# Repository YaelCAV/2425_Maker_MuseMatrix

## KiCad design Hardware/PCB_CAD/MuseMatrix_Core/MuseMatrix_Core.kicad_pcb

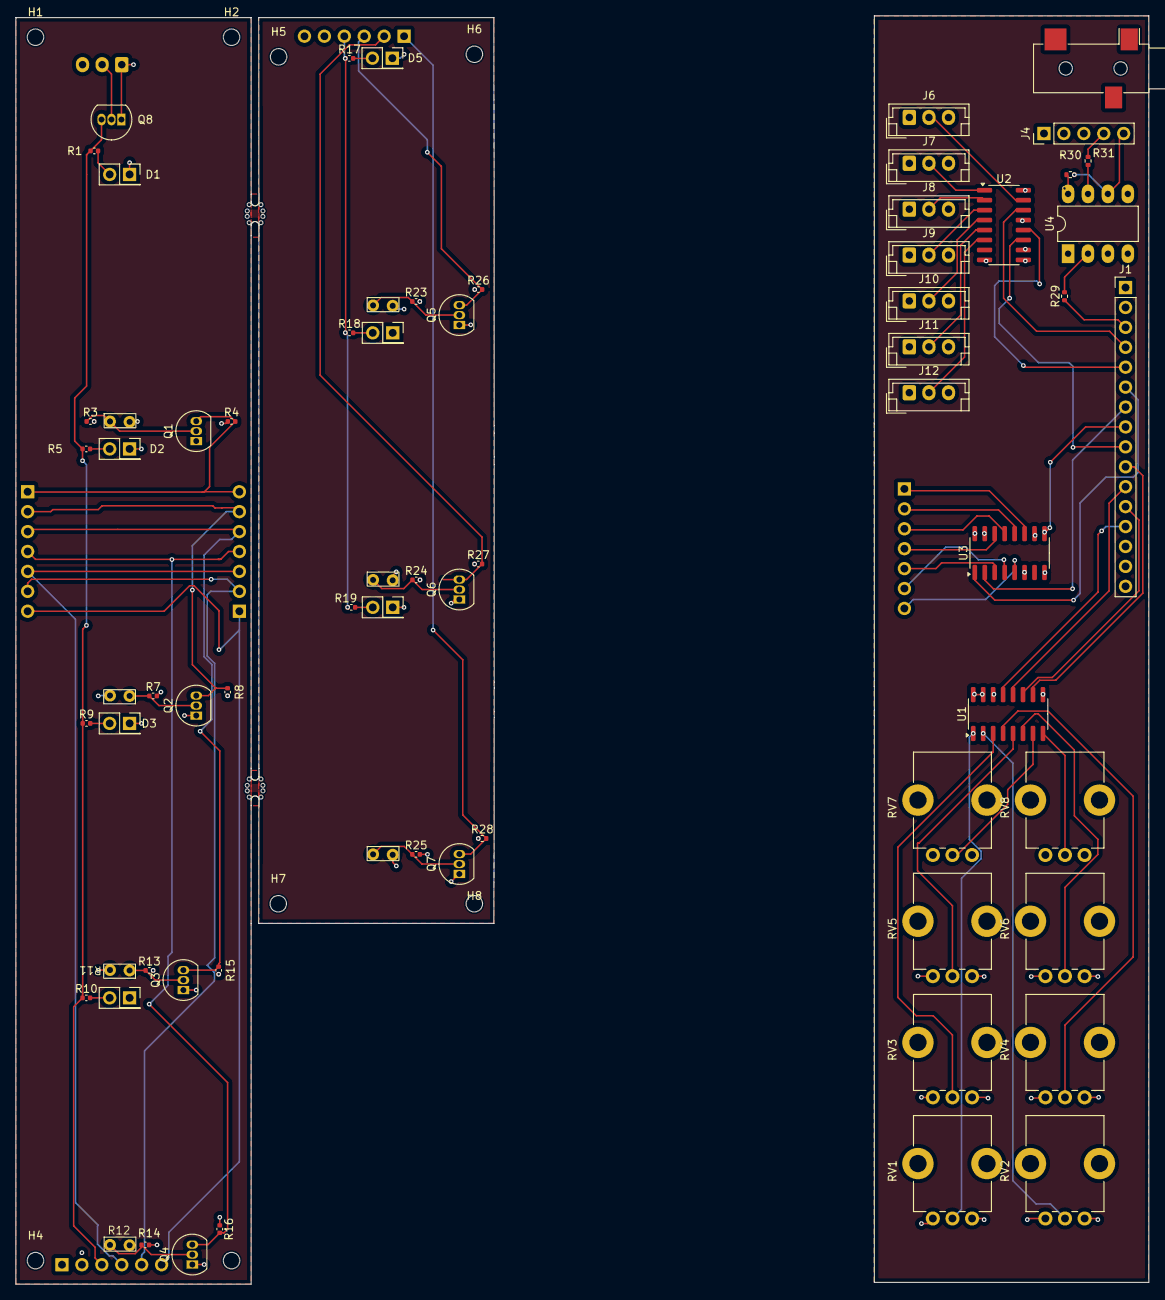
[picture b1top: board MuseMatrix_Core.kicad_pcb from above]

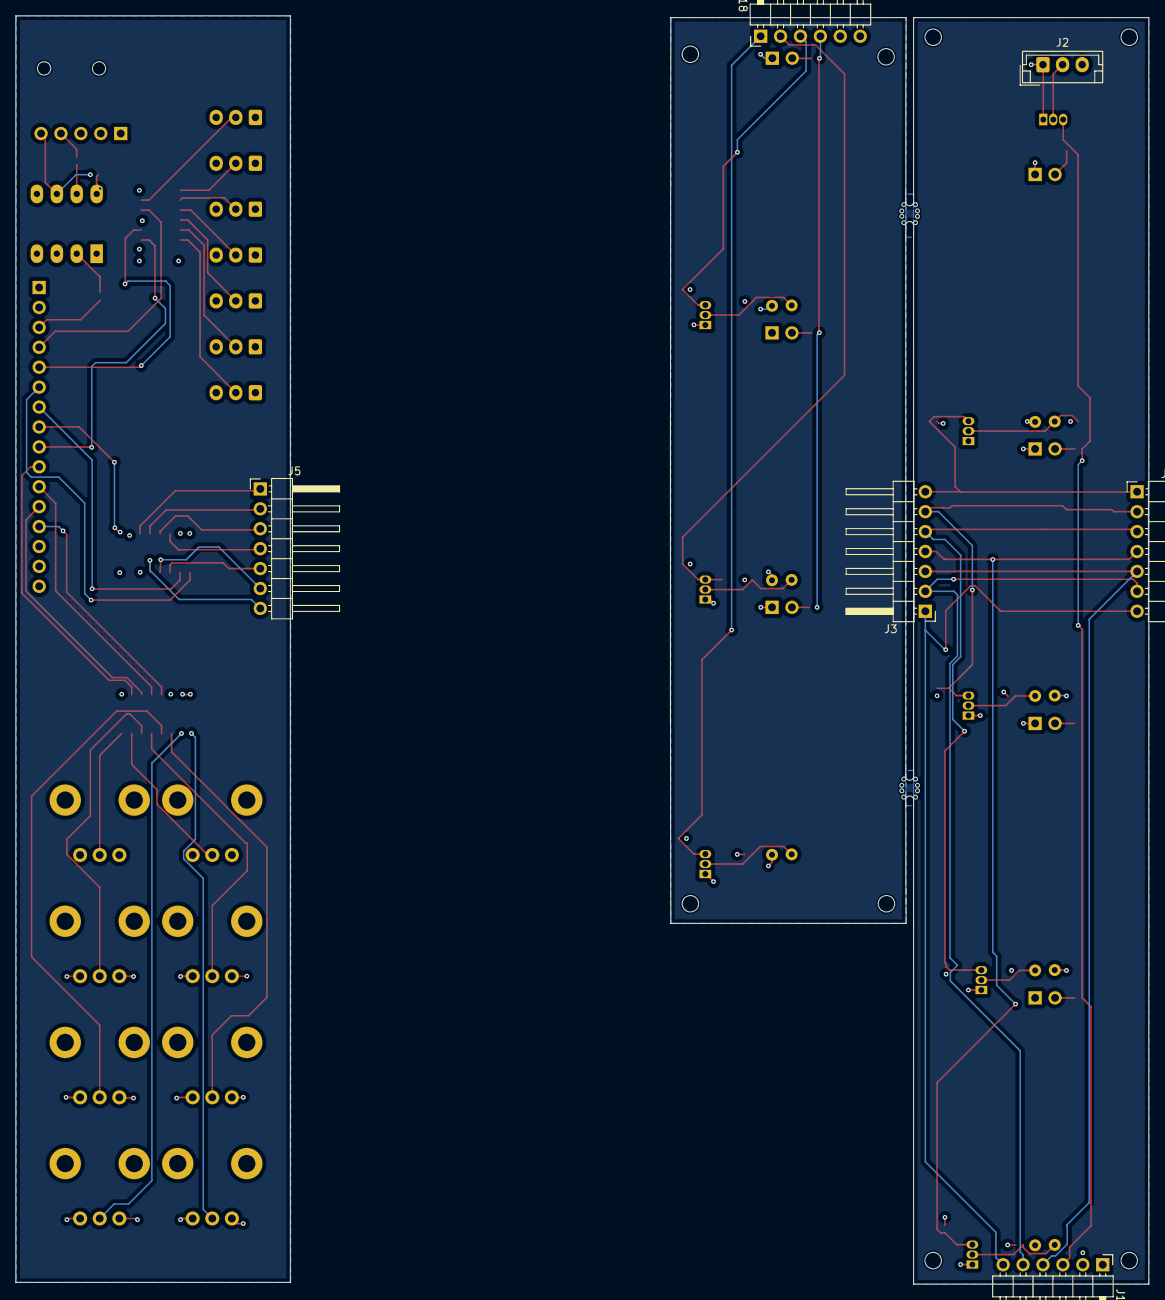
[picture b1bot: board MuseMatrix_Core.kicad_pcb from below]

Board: 4 copper layers, 144.5 x 161.7 mm, 84 parts (6 on the bottom side), 66 nets.

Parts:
D1, D2, D3, D4, D5, D6, D7: LED; PinSocket_2x01_P2.54mm_Vertical
H1, H2, H3, H4, H5, H6, H7, H8: MountingHole; MountingHole_2.1mm
J1: Raspberry_Pi_4; PinHeader_1x16_P2.54mm_Vertical
J2, J6, J7, J8, J9, J10, J11, J12: Conn_01x03_Pin; JST_EH_B3B-EH-A_1x03_P2.50mm_Vertical
J3: Conn_01x10_Socket; PinHeader_1x07_P2.54mm_Horizontal
J4: DIN-5; PinHeader_1x05_P2.54mm_Vertical
J5, J13: Conn_01x07_Socket; PinHeader_1x07_P2.54mm_Horizontal
J14: Jack-DC; Jack_3.5mm_CUI_SJ-3523-SMT_Horizontal
J17, J18: Conn_01x06_Pin; PinHeader_1x06_P2.54mm_Horizontal
Q1, Q2, Q3, Q4, Q5, Q6, Q7, Q8: 2N3904; TO-92_Inline
R1, R5, R9, R10, R17, R18, R19: 330; C_0402_1005Metric
R2, R6, R11, R12, R20, R21, R22: LDR07; LDR 2.5 horizontal
R3, R4, R7, R8, R13, R14, R15, R16, R23, R24, R25, R26, R27: 10k; C_0402_1005Metric
R28: 10k; R_0402_1005Metric
R29, R30, R31: 330; R_0402_1005Metric
RV1, RV2, RV3, RV4, RV5, RV6, RV7, RV8: R_Potentiometer; Potentiometer_Bourns_PTV09A-1_Single_Vertical
U1: MCP3008; SOIC-16_3.9x9.9mm_P1.27mm
U2: 74HC595; SOIC-16_3.9x9.9mm_P1.27mm
U3: 74HC165; SOIC-16_3.9x9.9mm_P1.27mm
U4: 6N138; DIP-8_W7.62mm_LongPads
mouse-bite-1mm-slot, mouse-bite-1mm-slot#2: VAL**; mouse-bite-1mm-slot

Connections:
+3.3V: J1.1 (3V3), J2.3, J6.3, J7.3, J8.3, J9.3, J10.3, J11.3, J12.3, J17.2, J18.5, R2.2, R4.1, R6.2, R8.1, R11.2, R12.2, R15.1, R16.1, R20.2, R21.2, R22.2, R26.1, R27.1, R28.1, R30.1, RV1.1, RV2.1, RV3.1, RV4.1, RV5.1, RV6.1, RV7.1, RV8.1, U1.15 (Vref), U1.16 (Vdd), U2.10 (~SRCLR), U2.16 (VCC), U3.15 (~CE), U3.16 (VCC), U4.8 (VCC)
/Column_7_Rows/Column_voltage: J2.2, Q8.2 (B)
/Column_7_Rows/column_voltage: J17.3, Q8.3 (C), R1.1, R5.1, R9.1, R10.1
/Column_7_Rows/column_voltage2: J18.4, R17.1, R18.1, R19.1
/Column_7_Rows/d1: J3.7, J13.1, Q1.3 (C), R4.2
/Column_7_Rows/d2: J3.6, J13.2, Q2.3 (C), R8.2
/Column_7_Rows/d3: J3.5, J13.3, Q3.3 (C), R15.2
/Column_7_Rows/d4: J3.4, J13.4, Q4.3 (C), R16.2
/Column_7_Rows/d5_0: J18.3, Q5.3 (C), R26.2
/Column_7_Rows/d5_1: J3.3, J13.5, J17.4
/Column_7_Rows/d6_0: J18.2, Q6.3 (C), R27.2
/Column_7_Rows/d6_1: J3.2, J13.6, J17.5
/Column_7_Rows/d7_0: J18.1, Q7.3 (C), R28.2
/Column_7_Rows/d7_1: J3.1, J13.7, J17.6
/Main_board/DATA_IN_595: J1.11 (GPIO17/SPI1_~CE1), U2.14 (SER)
/Main_board/DATA_OUT_165: J1.22 (GPIO14/UART_TXD), U3.9 (Q7)
/Main_board/LATCH_595: J1.15 (GPIO22/SDIO_CLK), U2.12 (RCLK)
/Main_board/LOAD_165: J1.16 (GPIO23/SDIO_CMD), U3.1 (~PL)
/Main_board/c0: J6.2, U2.15 (QA)
/Main_board/c1: J7.2, U2.1 (QB)
/Main_board/c2: J8.2, U2.2 (QC)
/Main_board/c3: J9.2, U2.3 (QD)
/Main_board/c4: J10.2, U2.4 (QE)
/Main_board/c5: J11.2, U2.5 (QF)
/Main_board/c6: J12.2, U2.6 (QG)
/Main_board/clock_165: J1.18 (GPCLK0/GPIO04), U3.2 (CP)
/Main_board/clock_595: J1.13 (GPIO27/SDIO_DAT3), U2.11 (SRCLK)
/Main_board/jst0: J5.1, U3.11 (D0)
/Main_board/jst1: J5.2, U3.12 (D1)
/Main_board/jst2: J5.3, U3.13 (D2)
/Main_board/jst3: J5.4, U3.14 (D3)
/Main_board/jst4: J5.5, U3.3 (D4)
/Main_board/jst5: J5.6, U3.4 (D5)
/Main_board/jst6: J5.7, U3.5 (D6)
/Main_board/midi_in: J1.8 (GPIO14/UART_TXD), R29.1
/Octaves board/ADC_clock: J1.23 (GPIO27/SDIO_DAT3), U1.13 (CLK)
/Octaves board/DATA_IN_ADC: J1.19 (GPIO18/SPI1_~CE0/PCM_CLK/PWM0), U1.11 (Din)
/Octaves board/DATA_OUT_ADC: J1.21 (GPIO17/SPI1_~CE1), U1.12 (Dout)
/Octaves board/select: J1.24 (GPIO15/UART_RXD), U1.10 (~CS/SHDN)
GND: D1.1 (K), D2.1 (K), D3.1 (K), D4.1 (K), D5.1 (K), D6.1 (K), D7.1 (K), J2.1, J6.1, J7.1, J8.1, J9.1, J10.1, J11.1, J12.1, J17.1, J18.6, Q1.1 (E), Q2.1 (E), Q3.1 (E), Q4.1 (E), Q5.1 (E), Q6.1 (E), Q7.1 (E), Q8.1 (E), R3.2, R7.2, R13.2, R14.2, R23.2, R24.2, R25.2, RV1.3, RV2.3, RV3.3, RV4.3, RV5.3, RV6.3, RV7.3, RV8.3, U1.9 (DGND), U1.14 (AGND), U2.8 (GND), U2.9 (QH'), U2.13 (~OE), U3.6 (D7), U3.8 (GND), U3.10 (DS), U4.3 (C2), U4.5 (GND)
unnamed: D1.2 (A), R1.2
unnamed: D2.2 (A), R5.2
unnamed: D3.2 (A), R9.2
unnamed: D4.2 (A), R10.2
unnamed: D5.2 (A), R17.2
unnamed: D6.2 (A), R18.2
unnamed: D7.2 (A), R19.2
unnamed: J4.4, R31.1
unnamed: Q1.2 (B), R2.1, R3.1
unnamed: Q2.2 (B), R6.1, R7.1
unnamed: Q3.2 (B), R11.1, R13.1
unnamed: Q4.2 (B), R12.1, R14.1
unnamed: Q5.2 (B), R20.1, R23.1
unnamed: Q6.2 (B), R21.1, R24.1
unnamed: Q7.2 (B), R22.1, R25.1
unnamed: RV1.2, U1.1 (CH0)
unnamed: RV2.2, U1.2 (CH1)
unnamed: RV3.2, U1.3 (CH2)
unnamed: RV4.2, U1.4 (CH3)
unnamed: RV5.2, U1.5 (CH4)
unnamed: RV6.2, U1.6 (CH5)
unnamed: RV7.2, U1.7 (CH6)
unnamed: RV8.2, U1.8 (CH7)
unnamed: R29.2, U4.2 (C1)
unnamed: R31.2, U4.7 (VO1)
unnamed: J4.5, R30.2, U4.6 (VO2)

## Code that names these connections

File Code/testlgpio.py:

import lgpio
import time

# GPIO Pins (BCM)
DATA_595 = 17
CLOCK_595 = 27
LATCH_595 = 22
LOAD_165 = 23
CLOCK_165 = 24
DATA_165 = 25

# Open GPIO chip
h = lgpio.gpiochip_open(0)

# Setup GPIO
lgpio.gpio_claim_output(h, DATA_595)
lgpio.gpio_claim_output(h, CLOCK_595)
lgpio.gpio_claim_output(h, LATCH_595)
lgpio.gpio_claim_output(h, LOAD_165)
lgpio.gpio_claim_output(h, CLOCK_165)
lgpio.gpio_claim_input(h, DATA_165)

def shift_out_595(data):
    lgpio.gpio_write(h, LATCH_595, 0)
    for i in range(8):
        lgpio.gpio_write(h, DATA_595, (data >> (7 - i)) & 1)
        lgpio.gpio_write(h, CLOCK_595, 1)
        lgpio.gpio_write(h, CLOCK_595, 0)
    lgpio.gpio_write(h, LATCH_595, 1)

def read_165():
    lgpio.gpio_write(h, LOAD_165, 0)
    lgpio.gpio_write(h, LOAD_165, 1)
    data = 0
    for _ in range(8):
        data = (data << 1) | lgpio.gpio_read(h, DATA_165)
        lgpio.gpio_write(h, CLOCK_165, 1)
        lgpio.gpio_write(h, CLOCK_165, 0)
    return data

try:
    while True:
        for col in range(8):
            shift_out_595(1 << col)
            time.sleep(0.01)
            row_data = read_165()
            print(f"C{col+1}: Rows={bin(row_data)[2:].zfill(8)}")
        print("---")
        time.sleep(0.5)

except KeyboardInterrupt:
    print("Exiting...")
    lgpio.gpiochip_close(h)

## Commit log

2025-03-10 pcb hierarchical update
2025-03-20 pcb update
2025-03-20 more pcb edit
2025-03-21 finished pcb + gerbers
2025-03-24 separated in 2 boards
2025-03-24 gerber column
2025-04-27 code added, bug with gpio library
